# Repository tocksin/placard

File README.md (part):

# Placard
## PLA computer
This project is a computer designed using some Programmable Logic Arrays (PLA) 
or Programable Array Logic (PAL) or Programmable Array Devices (PLD) chips.  
This started as a pure 7400-series chip computer, but changed over to using 
some PLA/PLDs to increase the usability while not greatly increasing the chip 
count.  The first PLA was created in 1970 by Texas Instruments.  The PAL was 
created in 1978 by Monolithic Memories which is owned by Lattice Semi today. 
There are some differences between the three types of chips, but this project 
isn't going to distinguished between them.

The design documents are in [docs/](docs/README.md), grouped by subject.

## Project goals
The project has some hard-goals to maintain:
- Use only through-hole chips similar to the 7400-series DIP chips (or PLA of course)
- Use only active production chips.  No hunting sketchy websites for parts.
- Design true von Neumann CPU from scratch.  No Harvard.  Bare-metal programming on the computer is a must (native compiler).
- Have a video output.  The video standard is open, but probably a legacy output (VGA/Composite/etc).
- Make the instruction set "fun" to program.  This means no racing the beam to draw the screen.  Counting instructions is not fun.
- A PS/2 keyboard and mouse, read by the machine's own PLD receiver.  No USB.
- Native storage capabilities.  Need to be able to save/load programs as you create them on the computer.

## Block diagram
Each block shows how many chips it uses (33 and a 3.3 V regulator on the main board; the expansion and cartridge slots add none, the 32K ROM cartridge itself has 3).  See [docs/architecture/CHIPS.md](docs/architecture/CHIPS.md) for the parts.

The drawing is made by `src/scripts/gen_block_diagram.py` (CPU on the left, memory, I/O and audio in the middle, video on the right); rerun it when the design changes.

The I/O circuitry (SNES pads, SD card, PS/2 keyboard and mouse) is drawn as a schematic in
[docs/architecture/IO.md](docs/architecture/IO.md#schematic) (`schematics/placard_io_schematic.png`).
The audio circuitry (sample read, DAC register, R-2R ladder, audio line out jack) is drawn in
[docs/sound/SOUND.md](docs/sound/SOUND.md#schematic) (`schematics/placard_video_audio_schematic.png`).

The real schematic and PCB layout are a KiCad project in [kicad/](kicad/).

To build a board one chip at a time, testing each with a multimeter as it goes in, follow [docs/hardware/BRINGUP.md](docs/hardware/BRINGUP.md); it has a bring-up test ROM that checks the CPU and memory and shows the I/O on the screen.

## Memory Map
The Placard has 64kB of memory arranged in a 16-bit address bus and 8-bit databus.  The video RAM starts at x6020 and ends at xFFFF, and each row's mode byte (color mode and line repeat) is at x5A20 + row.  There is a 64kB RAM and a 64kB ROM behind the same addresses.  The address space is divided into eight 8kB sections, and a write-only map register at x5000 picks whether each section reads from the RAM or the ROM.

- **Writes always go to the RAM**, even in a section mapped to ROM.  The write strobe (/WE) is not decoded by address, so a write in the I/O window x5000-x53FF also lands in the RAM underneath it.
- **The map register** is a CD74ACT273E clocked by /MAP_WR from the I/O decode PLD; it latches the source bus at the end of the write.  Bit n = 1 makes section n read from RAM, 0 from ROM.  Bit 2 maps x4000-x4FFF and x5400-x5FFF, because x5000-x53FF is the I/O window.  It is write only, so software keeps a copy of the last value it wrote.
- **At power-up every section reads as ROM.**  RUN from the ROM cartridge holds the register's /MR low while the cartridge loads its SRAM and the CPU is held, so the CPU boots from ROM ([docs/architecture/ROM.md](docs/architecture/ROM.md#loading-the-cartridge)).
- **x5000-x53FF is the I/O window.**  The memory control PLD keeps both the RAM and the ROM off the bus there, so I/O always has priority.
- **Only `[Y,X]` reaches the I/O window**; `[0,D]` and `[0,X]` only address the zero page.
- **Video reads always read the RAM** (memory control PLD); only CPU reads follow the map.  The CPU can run code from the ROM under the video area while the screen shows the RAM, and a program that wants to read the video RAM maps that section to RAM.
- **The ROM is grouped by 8 KB section.**  The machine's 32K ROM (x8000-xFFFF, read at x0000-x7FFF too) holds the boot loader, the library, BASIC and a loader that runs the DOS and programs from the SD card, and each map section holds one kind of thing: section 7 what almost every program uses (jump table, core routines, PS/2 keyboard, pads, mouse, line input), section 6 the files (SD card driver, FAT reader and writer), section 5 BASIC, section 4 the loader, sound driver and font.  A program that maps a section to RAM gives up just that; the font is read through a zero page pointer (`FONT_PG`), so a program can put its own font anywhere.  The library runs in place.  The boot loader copies the library's RAM code to x1F00, gives each expansion card a chance to run its own boot code (like the Apple II), then maps sections 0 and 2 to RAM (map = 05) and starts the loader.  A development ROM (64K cartridge) adds one program in the first 32K, run in place at x6000-x7FFF and x2000-x3FFF, or copied to RAM x0000 for the older demos.  See [docs/architecture/ROM.md](docs/architecture/ROM.md) and [docs/software/DOS.md](docs/software/DOS.md).
- **After a map write**, the next instruction must not be fetched from a section whose map bit that write changed, unless the ROM and RAM hold the same byte there (the new map arrives 2.6 ns too late for that fetch).  Copying the ROM into the RAM underneath and then switching the section is safe.  See [docs/timing/TIMING.md](docs/timing/TIMING.md#video-and-the-rest).

The memory control PLD (`ATF22V10_MEM_CTRL.pld`) makes /ROM_OE and /RAM_OE from the address, the map, RW and PIXEL_ENABLE, using only the low half of each clock.  The RAM's /WE comes from the Sync PLD, off an early tap of the clock ([docs/timing/WE_TIMING.md](docs/timing/WE_TIMING.md)).  The I/O decode PLD (`ATF22V10_IO_DECODE.pld`) makes the upper RAM/ROM chip select (/CE_HI) and the I/O strobes.

The RAM is two AS7C256C-15PCN (32K × 8, 15 ns) chips.  The ROM is one more AS7C256C-15PCN on the 32K ROM cartridge, loaded at power-up from one AT28C256 EEPROM by the cartridge while it stalls the CPU ([docs/architecture/ROM.md](docs/architecture/ROM.md#loading-the-cartridge)).  See [docs/architecture/CPU.md](docs/architecture/CPU.md#memory-parts) and [docs/timing/TIMING.md](docs/timing/TIMING.md).

| Address | Map bit | Function  |
|---------|---------|------|
| x0000-x1FFF | 0 | RAM/ROM (zero page, program variables, library RAM code at x1F00; ROM: reset jump) |
| x2000-x3FFF | 1 | RAM/ROM (development ROM: program) |
| x4000-x4FFF | 2 | RAM/ROM (program data; FAT variables and buffer at x4D00-x4FFF) |
| x5000-x53FF | none | I/O window (see below) |
| x5400-x5FFF | 2 | RAM/ROM (mode bytes at x5A20-x5BFF, audio buffer at x5DF3-x5FFF) |
| x6000-x7FFF | 3 | RAM/ROM (Video Memory from x6020; development ROM: program from x6000) |
| x8000-x9FFF | 4 | RAM/ROM (Video Memory; ROM: vectors x8000, loader and the end of BASIC x8100, sound driver x9200, font x9700, LIB_RAM copy x9F00) |
| xA000-xBFFF | 5 | RAM/ROM (Video Memory; ROM: BASIC) |
| xC000-xDFFF | 6 | RAM/ROM (Video Memory; ROM: files: SD card driver xC000, FAT reader xC800, FAT writer xD600) |
| xE000-xFFFF | 7 | RAM/ROM (Video Memory; ROM: PS/2 keyboard, pads, mouse, line input, menu hook, slot helpers, core routines xF400, jump table xFB00, boot loader xFD00) |

The drawing is made by `src/scripts/gen_memory_map.py`; rerun it when the map changes.

### I/O window
Each I/O page has its own select from the I/O decode PLD (revision 07), made straight from the address and valid about 13 ns into the clock.  A write is the select with /WE: devices latch the source bus on the rising edge at the end of /WE.  A read is the select with Q0 low (the LOAD_MEM clock, when the CPU latches the bus into D), and nothing waits for STALL.  The shared port is described in [docs/architecture/IO.md](docs/architecture/IO.md) and the expansion slots in [docs/architecture/EXPANSION.md](docs/architecture/EXPANSION.md).

| Address | Select | R/W | Function |
|---------|--------|-----|----------|
| x5000-x50FF | /P0 (write: /MAP_WR from the Sync PLD) | W | ROM/RAM map register (built) |
| x5000-x50FF | /P0 and Q0 | R | Video line counter, V9:V2 (built) |
| x5100-x517F | /EXP1 | R/W | Expansion slot 1 |
| x5180-x51FF | /EXP3 | R/W | Expansion slot 3 |
| x5200-x52FF | /PORT and /WE | W | Shared port latch (port PLD registers): SD card SCK, MOSI and /CS, SNES pad clock and latch, PS/2 lines; a write to x5202/x5203 also re-arms the PS/2 receiver |
| x5200-x52FF | /PORT and Q0 | R | Shared port: SD MISO and the free PS/2 clock (x5200), SNES pad data (x5201), PS/2 receiver byte (x5202) and ready flag (x5203) |
| x5300-x537F | /EXP2 | R/W | Expansion slot 2 |
| x5380-x53FF | /EXP4 | R/W | Expansion slot 4 |

### Sound
The video circuit reads one 8-bit sample per scan line from x5DF3-x5FFF (525 bytes, one frame) and plays it through a 74HCT574 and a resistor ladder DAC, at the line rate of 31.47 kHz.  80h is silence.  The library's sound driver (`snd_update` once a frame, with `snd_tone`, `snd_beep`, `snd_note`, `snd_noise` and `snd_play`) refills the buffer behind the line being played.  See [docs/sound/SOUND.md](docs/sound/SOUND.md).

### Video line read
A read anywhere in x5000-x50FF returns the upper 8 bits of the video line counter, V9:V2.  The V counter in the V Counter PLD counts 499 to 1023, and one 74F541 enabled by /P0 and Q0 puts V9:V2 on the data bus.  The ROM/RAM map register shares the page but is write only, so there is no conflict.  Read it with `ld 0x50, y` then `ld [y,x], ac`.

- **It is a single byte**, so it can't tear between reads.
- **Resolution is 4 lines** (128 us).  Visible rows start at V = 544, so `row / 4 = value - 136`.  A value below 136 means vertical blanking.
- **There is no frame counter.**  Software keeps time by polling: each time the value goes down (from 255 back to 124), a frame has passed.  At the FPGA's 25.000 MHz clock a frame is 525 lines, about 16.8 ms (59.5 Hz).
- **Software must poll at least once per frame**, or it misses a wrap.  Elapsed time is then frames x 16.8 ms plus the line position for finer detail.

## Video
The video is designed to be 640x480 VGA 60Hz standard.  This means a 25.175 MHz clock.  This requires two counters: a horizontal and vertical.  They count 800 and 600 pixels.  This needs a 10-bit counter for each.  The counters form the RAM address space to read the pixel values.  The video memory is organized in a non-traditional way with H,V instead of V,H.

### Line repeat
Bits 3:2 of a row's mode byte make each byte of video memory show on 1, 2 or 4 lines (640 × 480, 240 or 120).  A full 2x screen leaves 20 KB of the video area free (the even pages x60, x62 ... xFE) and a full 4x screen 30 KB.  The audio slot PLD remaps four row address bits, so no chips were added.  See [docs/video/VIDEO.md](docs/video/VIDEO.md#line-repeat).

### Text demo
`src/scripts/text_demo.asm` draws a demo screen with the CPU and keeps a test running on it: 80 column text (2 colors, 1x, under row tints: blocks of the 7 tints roll down over the text, with a second of rest between), a 16 color band (4 bpp, 4x), 40 column text (2 bpp, 2x) and a 256 color band (8 bpp, 4x) with "256" in shades of red, blue and green and a turning rainbow ring.  Each frame it tests one page of RAM (85 pages: x0100-x1EFF, x2000-x4FFF, x5400-x59FF and x5C00-x5CFF, 14 patterns each, with a progress bar, pass and error counts) and updates a frame counter, an uptime clock, a spinner, a turning color wheel, the ring and a message that scrolls a pixel a frame.  H shows the same picture on the 160-read rows of a rev B board (80 column text in 4 colors, 16 colors at 320 across, 256 colors at 160 across: smoothed letters and digits, round wheel dots, a rounder ring; [docs/video/HIRES.md](docs/video/HIRES.md)) and back.  It runs from the SD card (`TEXT.PLC`, `gen_text_demo_sd.py`, in the demo menu), and `src/scripts/text_demo_sim.py` runs and checks it in the simulator (`--gif` makes an animation).  `gen_text_demo_sd.py` makes the SD card version (`TEXT.PLC`, in the demo menu), whose RAM test covers only the RAM the program leaves free ([docs/software/MENU.md](docs/software/MENU.md#the-text-demo-on-the-card)).

### DOS, BASIC and demo menu
The machine ships the 32K ROM image (`src/scripts/rom32.masm`, `build\rom32.bat`): the boot loader, the library, PLACARD BASIC (a 16-bit integer BASIC with strings, graphics, sound and SAVE/LOAD on the card, [docs/software/BASIC.md](docs/software/BASIC.md)) and a loader that runs `.PLC` programs from the SD card.  The DOS is one of those programs (`DOS.PLC`, `src/scripts/dos.masm`).  At power-up the loader runs the program named in `BOOT.CFG`, or the DOS's file browser (hold Esc) that runs, deletes and picks the boot program, with a command line for `LOAD` and `SAVE` of memory as files.  With no card, or no `DOS.PLC` on it, BASIC starts.  Ctrl+B in the browser starts BASIC.  The demo menu is one of those programs (`MENU.PLC`, `src/scripts/menu.masm`): the CPU test, pi, Mandelbrot, the Game of Life, the Boing ball, the 3D ships, the ray caster, the side scroller, the textured ray caster and the text demo run in turn, each until it is done or for 2 minutes (Mandelbrot 3); Esc in any program shows the menu (Up / Down and Enter, or 1-9 and 0), a program picked there runs until Esc, and after 2 minutes with no key the menu goes back to running them in turn.  The `sdcard/` folder holds the files for the card; `src/scripts/test_dos.py`, `test_menu.py` and `test_basic.py` check them in the simulator; the `.BAS` files on the card are BASIC examples.  See [docs/software/DOS.md](docs/software/DOS.md), [docs/software/MENU.md](docs/software/MENU.md) and [docs/architecture/ROM.md](docs/architecture/ROM.md#the-32k-image).

### Pinboard
`sdcard/PINBOARD.PLC` (`src/scripts/pinboard.masm`, `pinboard.vm`, `gen_pinboard.py`) is a windowed desktop: cards pinned on a board, moved, stacked and taken down with the PS/2 mouse or the keys.  The Files card browses the SD card, runs its programs, shows its pictures in the photo viewer and plays its sound files in the sound player, and Pinboard comes back when one ends; the Clock card keeps the time you set, the Calc card is a whole-number calculator, and the Editor card edits a text file from the card and saves it.  The Display card switches the screen between 640 x 480 in 2 colors and, on a rev B board, 640 x 240 in 4 colors or 320 x 240 in 16.  It is written in the language of BASIC's interpreter, with machine code for the characters and the pointer.  `src/scripts/test_pinboard.py` checks it in the emulator's core ([docs/software/PINBOARD.md](docs/software/PINBOARD.md)).

### Game demos
Four demos show what the CPU can do with no sprite or collision hardware.  The first three are written by a Python generator (the tables, the unrolled drawing code and a bit-exact model of the picture), and each has a simulator test that checks every frame against the model.

`sdcard/RAYCAST.PLC` (`gen_raycast.py`, which writes `src/scripts/raycast_sd.asm`) is a ray caster: an 80 × 112 view at 8 bpp (4x line repeat) of a maze with shaded, two-tone walls and a dithered floor and ceiling, walked by a demo script until a key or pad button takes over (arrow keys or SNES pad 1: Up / Down walk, Left / Right turn).  A view takes 143k-170k clocks (a column about 2,000), so it runs at the full 60 views a second using under 40 % of each frame.  It is in the demo menu and `src/scripts/test_raycast_sim.py` checks it.

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
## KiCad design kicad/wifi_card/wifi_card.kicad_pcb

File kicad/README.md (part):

# KiCad project

Date: 2026-11-21

The Placard schematic and PCB layout, one KiCad project for the main board
and one for each cartridge.  The files are saved by KiCad 9, so open them
with KiCad 9 or newer.  Board revisions are in
[docs/hardware/RELEASES.md](../docs/hardware/RELEASES.md): rev A is the
board as ordered (git tag `rev-A`), and the files here are the working
rev B.

| File | What it is |
|------|------------|
| `placard.kicad_pro` | the project; open this in KiCad |
| `placard.kicad_sch` | the schematic's root sheet (A3): one box per sheet, laid out like the block diagram |
| `power.kicad_sch` ... `expansion.kicad_sch` | the ten sheets (power and clock, control, PC and address mux, ALU and registers, data bus, memory and I/O decode, video timing, video and audio out, shared port, expansion slots), docs/hardware/SCHEMATIC_PLAN.md |
| `cartridge_64k/` | the 64K ROM cartridge (5 chips), its own project (`cartridge_64k.kicad_pro`, one sheet and a routed 4-layer board), using the same `lib/` |
| `cartridge_32k/` | the 32K ROM cartridge (3 chips), its own project (`cartridge_32k.kicad_pro`, one sheet and a routed 4-layer board), using the same `lib/`; mounting hole H1 at the same place as on the 64K board |
| `memory_card/` | the 512K memory expansion card (3 chips, docs/architecture/MEMCARD.md), its own project (`memory_card.kicad_pro`, one sheet and a routed board), using the same `lib/`.  The sheet is written by `gen_kicad_schematic.py --memcard`, which leaves the other sheets alone, and the board by `gen_kicad_memcard_pcb.py` (KiCad 9), which keeps an existing board unless run with `--force` |
| `wifi_card/` | the WiFi expansion card (one PLD and an ESP32-C3-DevKitM-1 board, docs/architecture/WIFICARD.md), its own project (`wifi_card.kicad_pro`, one sheet and a board with the parts placed, not routed), using the same `lib/`.  The sheet is written by `gen_kicad_schematic.py --wificard` and the board by `gen_kicad_wificard_pcb.py` (KiCad 9), which keeps an existing board unless run with `--force` |
| `placard.kicad_pcb` | the main board, routed: 4 layers (F.Cu, In1.Cu = GND, In2.Cu = VCC, B.Cu) |
| `lib/placard.kicad_sym` | PLD symbols: `ATF22V10C` (generic) and one `ATF22V10C_<name>` per `.pld` file, with its pin names |
| `lib/placard_parts.kicad_sym` | other project symbols: `AS7C256C` SRAM, `Expansion_Slot`, `Cartridge_Slot`, `SNES_Pad_Socket`, `PS2_Dual_Stacked`, `USB_C_Power` |
| `lib/placard_std.kicad_sym` | copies of the stock KiCad symbols the sheets use (74xx, R, C, D, connectors, regulator, the cartridge EEPROM `28C256`, and the power symbols `+5V`, `GND`, `+3V3`, `GNDA`, `PWR_FLAG`) with larger pin text, written by `src/scripts/gen_kicad_std.py` |
| `lib/placard.pretty/` | project footprints: the main board's connectors and switches (written by `src/scripts/gen_kicad_connectors.py`), and kit versions of KiCad's DIP socket footprints (`DIP-nn_..._Socket_Puller`: chip-puller room on User.Eco1, part number in silkscreen) and of the axial resistor (`..._Value`: value in silkscreen), written by `src/scripts/gen_kicad_kit_footprints.py`, and copies of the KiCad 9.0.6 footprints the boards use (capacitors, diodes, LED, pin header, oscillator, TO-92, SIP resistor array, mounting holes, net tie; KiCad 9 format), written by `src/scripts/gen_kicad_stock_footprints.py` |
| `lib/placard.3dshapes/` | 3D models (STEP) for the connectors, switches and polyfuse, named after their footprints and referenced as `${KIPRJMOD}/lib/placard.3dshapes/...`, so they show in any KiCad version without a 3D library path; written by `src/scripts/gen_kicad_3d_models.py` (CadQuery), which also copies in KiCad's own models for SW2, J7 and J13, and KiCad's models for the stock, socket and resistor footprints, copied by `src/scripts/gen_kicad_stock_footprints.py` |
| `sym-lib-table`, `fp-lib-table` | point KiCad at the project libraries |
| `fab/` | the rev A Gerber and drill files as ordered ([fab/README.md](fab/README.md)) |

The main board is 290 x 215 mm (290 wide, the keyboard's width; 215 deep, so
kit builders have room), 4 layers, placed and routed.

The back edge carries USB-C power, audio line out, VGA and the stacked PS/2;
the left side the power switch, reset button and SD card; the front edge the
two SNES ports.  The cartridge and the four expansion cards stand up
through the case top.  Every DIP sits in a socket footprint with 2.5 mm of
chip-puller room clear past each socket end, and Cn sits beside Un.
`src/scripts/gen_board_pictures.py` draws the two pictures (and the
cartridge pictures in [EXPANSION.md](../docs/architecture/EXPANSION.md))
from the board files without changing them; rerun it after a layout change.

The board file is edited in KiCad and by the autorouter, so it is the
source.  `src/scripts/gen_kicad_pcb.py` made the first outline and placement
and `src/scripts/gen_kicad_cart_pcb.py` the cartridges' placement; do not
run either on the boards now (the cartridge script leaves an existing board
alone unless given `--force`).  The first placement drawings are in
[docs/archive/](../docs/archive/README.md).

The footprints KiCad has no part for (cartridge slot, expansion slots,
PS/2, SNES, the power switch, the relay) are written by
`src/scripts/gen_kicad_connectors.py`.  The SNES sockets were measured from
the part; the others are drawn from typical dimensions for the part family,
so check them against the parts when the rev A boards arrive.
Their 3D models (`src/scripts/gen_kicad_3d_models.py`) are drawn at typical
dimensions too, with the leads put on the footprint pads.  J4 (SD), J7 (VGA),
F1 and SW2 use project copies of KiCad's footprints (`placard:` library) only so
they can point at the project's models; the pads are KiCad's.
The schematic rules (which chips go on which sheet, numbering, and how
the sheets are drawn) are in [docs/hardware/SCHEMATIC_PLAN.md](../docs/hardware/SCHEMATIC_PLAN.md).  Parts and U-numbers come from
[docs/architecture/CHIPS.md](../docs/architecture/CHIPS.md); the PLD pinouts come from the `.pld` files
in `src/`.

Every part carries Manufacturer and MPN fields (empty where no part number
is chosen yet), set from the `MPN` table in `src/scripts/gen_kicad_schematic.py`,
so KiCad's BOM export lists them.  `src/scripts/gen_bom.py` writes one grouped
bill of materials per assembly (main board, 64K and 32K cartridges, case),
indexed in [docs/bom/BOM.md](../docs/bom/BOM.md), each as .md and .csv, including the
bare PCBs, sockets, shells and screws that are not on the schematic.

Backups, autosaves, lock files, `*.kicad_prl` (per-user view settings) and
`fp-info-cache` are git-ignored.

## PLD symbols

`src/scripts/gen_kicad_symbols.py` writes `lib/placard.kicad_sym` from the
`PIN` statements in `src/pld/*.pld`; rerun it after changing a PLD's pins
(it overwrites the whole library).  The pins are placed for the schematic,
not in pin-number order: the script's `LAYOUT` table puts inputs on the
left and outputs on the right, buses together in bit order, and each
function's pins in their own group.  Where one PLD does two unrelated jobs
(the audio PLD's /AC_SEL, the port PLD's pad read, the memory control's
RUN input) a dashed line across the box separates them.  Active-low pins are
`/NAME`, VCC (24) is on top and GND (12) underneath, unused pins are `nc`
(no-connect type), and the `.pld` file name is under the part number.  The
script stops if a `.pld`'s pins and its `LAYOUT` entry no longer match.
Each symbol has the footprint `Package_DIP:DIP-24_W7.62mm` and the
ATF22V10C datasheet link.

## Other symbols

`src/scripts/gen_kicad_parts.py` writes `lib/placard_parts.kicad_sym`, in
the same style, for the parts KiCad's libraries do not have: the AS7C256C
SRAM, the expansion slot (Molex 87715-9106 as the cartridge slot, contacts A1-A32 and B1-B32)
and the cartridge slot (Molex 87715-9106, 2 x 32 keyed, contacts A1-A32
and B1-B32), as in EXPANSION.md, with the +5 V and GND contacts stacked on
one pin each, the SNES pad socket (IO.md) and
`USB_C_Power`, the 5 V input: a power-only 6-contact USB-C receptacle
(GCT USB4125, footprint `placard:USB_C_Receptacle_GCT_USB4125_6P_HandSolder`:
KiCad's USB4125 footprint with the SMD pads 1.5 mm longer for the iron, made by gen_kicad_connectors.py)
with a 5.1k resistor from CC1 and from CC2 to GND so a charger gives 5 V.  Make
changes in the script, since rerunning it overwrites the library.

Every symbol, footprint and 3D model the sheets and boards use is in `lib/`
(since 2026-10-26): the projects' library tables list only the placard
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
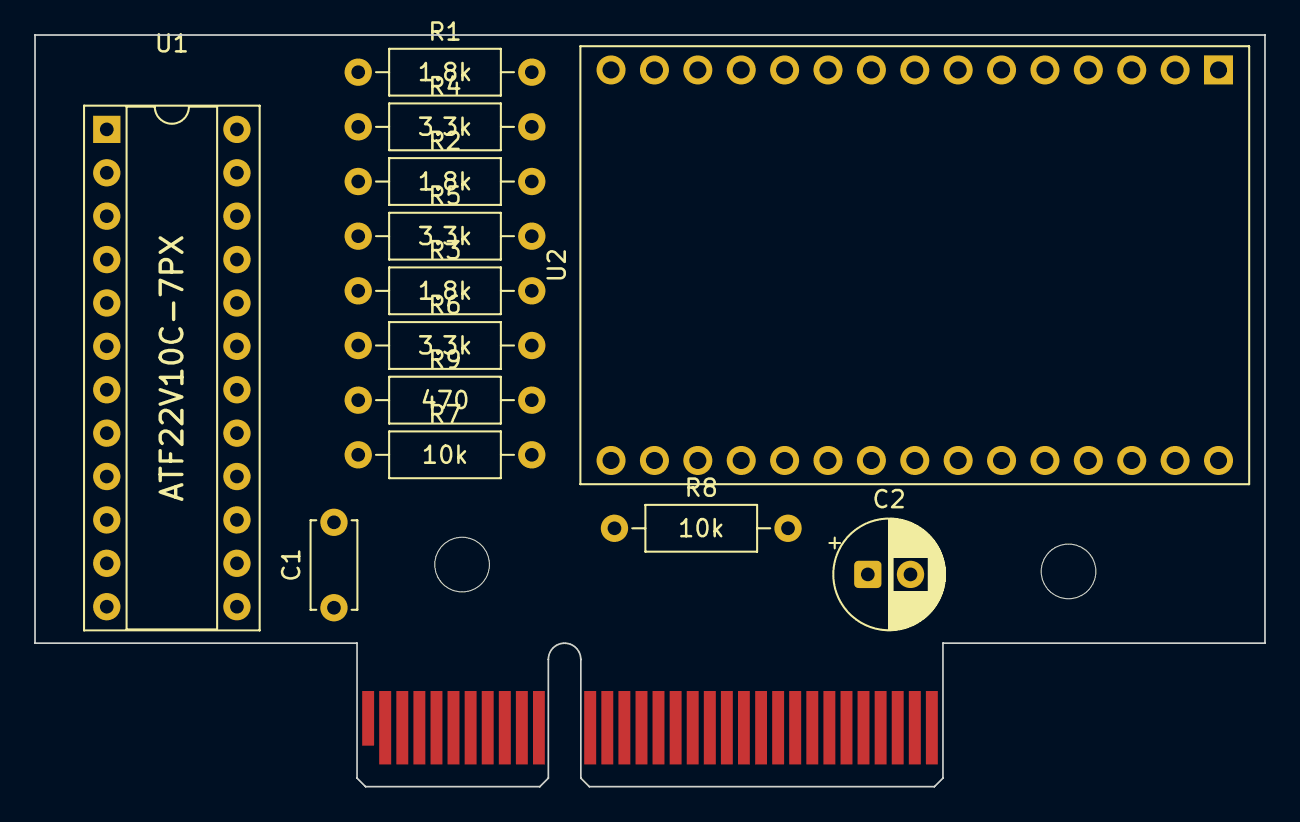
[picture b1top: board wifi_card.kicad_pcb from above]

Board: 4 copper layers, 72.0 x 44.0 mm, 16 parts (0 on the bottom side), 26 nets, no tracks yet.

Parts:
C1: 100n; C_Disc_D5.0mm_W2.5mm_P5.00mm
C2: 220u; CP_Radial_D6.3mm_P2.50mm
H1, H2: M3; MountingHole_3.2mm_M3
J1: Card edge (87715-9106 mate); Card_Edge_87715-9106
R1, R2, R3: 1.8k; R_Axial_DIN0207_L6.3mm_D2.5mm_P10.16mm_Horizontal_Value
R4, R5, R6: 3.3k; R_Axial_DIN0207_L6.3mm_D2.5mm_P10.16mm_Horizontal_Value
R7, R8: 10k; R_Axial_DIN0207_L6.3mm_D2.5mm_P10.16mm_Horizontal_Value
R9: 470; R_Axial_DIN0207_L6.3mm_D2.5mm_P10.16mm_Horizontal_Value
U1: ATF22V10C-7PX; DIP-24_W7.62mm_Socket_Puller
U2: ESP32-C3-DevKitM-1-N4X; ESP32-C3-DevKitM-1

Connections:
+5V: C1.1, C2.1, J1.A2, J1.B2, U1.24, U2.13, U2.14
/DATABUS0: J1.A23, U1.7
/DATABUS1: J1.B13, U1.8
/DATABUS2: J1.B15, U1.18
/DATABUS3: J1.B17, U1.19
/DATABUS4: J1.B19, U1.20
/DATABUS5: J1.B23, U1.21
/DATABUS6: J1.B25, U1.22
/DATABUS7: J1.B29, U1.23
GND: C1.2, C2.2, J1.A1, J1.A11, J1.A12, J1.A21, J1.A31, J1.B1, J1.B11, J1.B18, J1.B21, J1.B26, J1.B30, J1.B31, J1.B32, R4.2, R5.2, R6.2, R7.2, R8.2, U1.12, U2.6, U2.8, U2.12, U2.15, U2.19, U2.22, U2.27, U2.30
unnamed: J1.A22, U1.4
unnamed: J1.B9, U1.5
unnamed: J1.B7, U1.6
unnamed: J1.A10, U1.3
unnamed: J1.A16, U1.2
unnamed: J1.B24, U1.1
unnamed: R7.1, U1.9, U2.25
unnamed: R8.1, U1.10, U2.26
unnamed: R3.1, U1.16
unnamed: R2.1, U1.15
unnamed: R9.1, U1.17
unnamed: R1.1, U1.14
unnamed: R1.2, R4.1, U2.24
unnamed: R2.2, R5.1, U2.23
unnamed: R3.2, R6.1, U2.11
unnamed: R9.2, U2.7

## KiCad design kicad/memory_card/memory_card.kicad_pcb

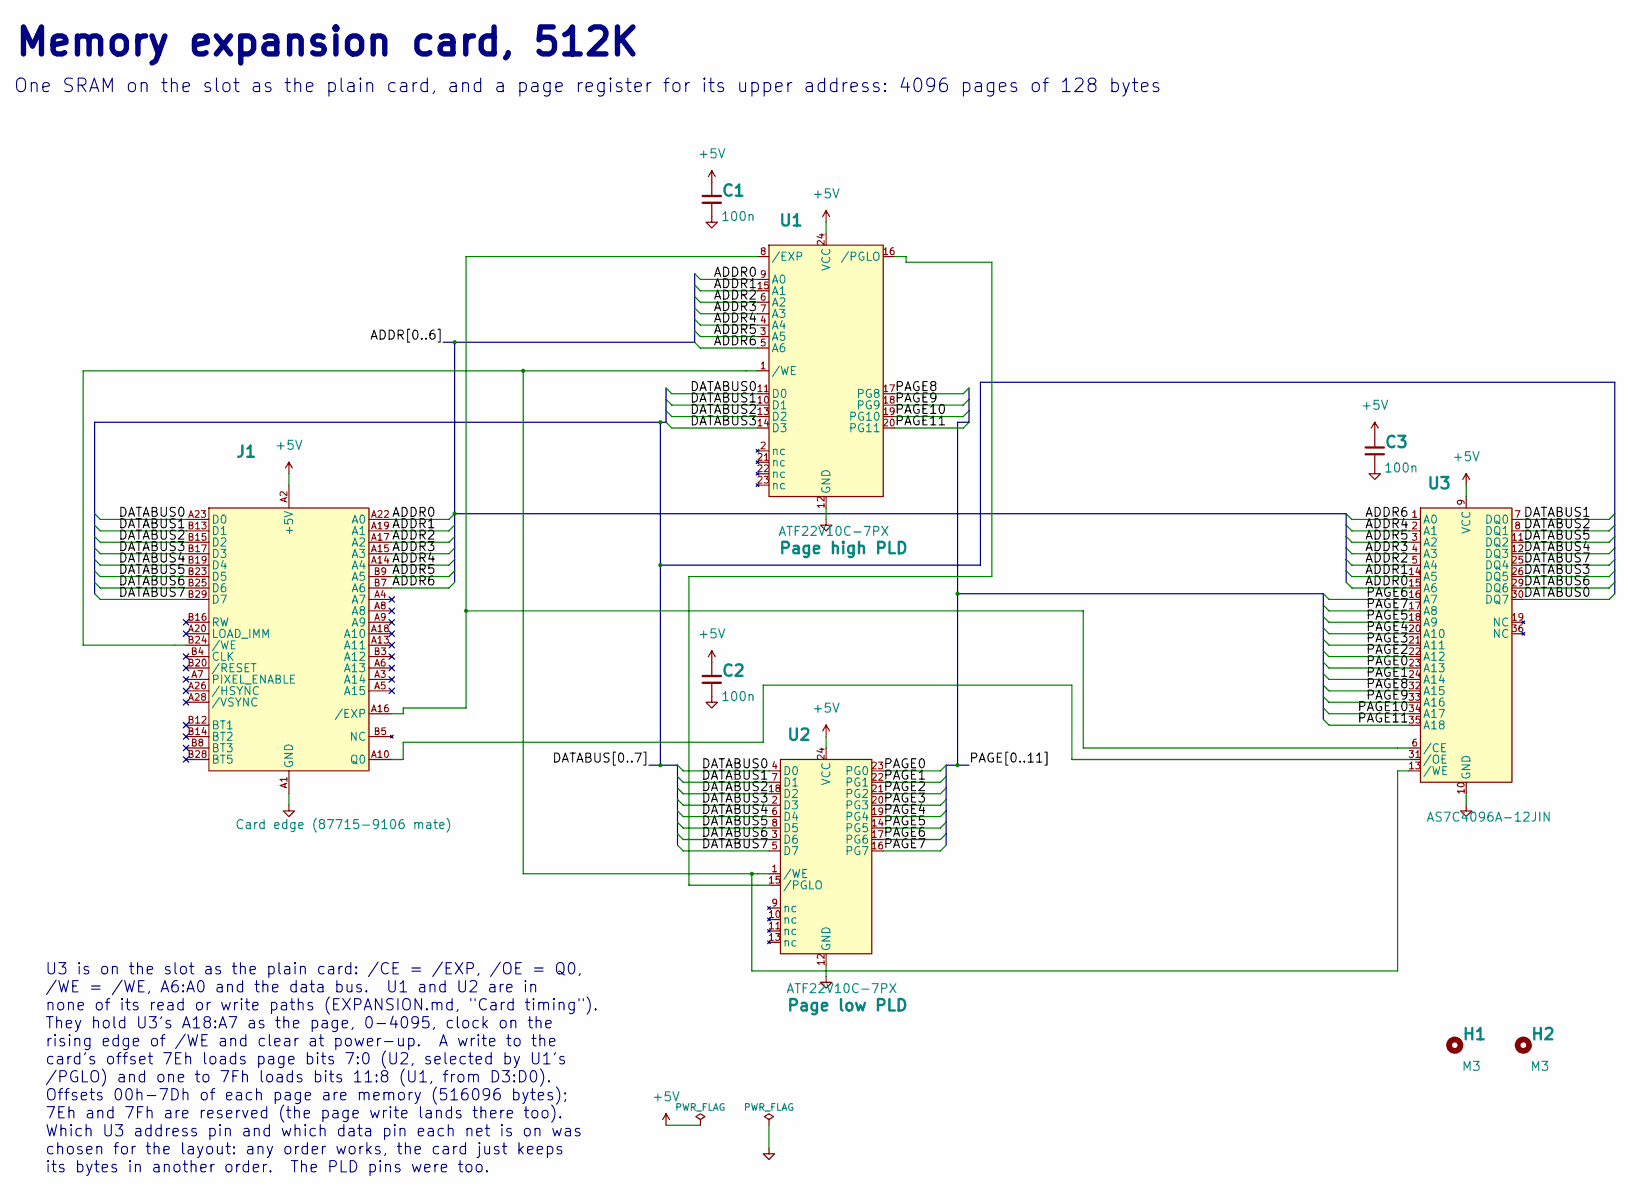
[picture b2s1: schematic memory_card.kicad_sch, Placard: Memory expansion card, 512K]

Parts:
C1, C2, C3: 100n; C_Disc_D5.0mm_W2.5mm_P5.00mm; MPN FG28X7R1H104KNT00
H1, H2: M3; MountingHole_3.2mm_M3
J1: Card edge (87715-9106 mate); Card_Edge_87715-9106
U1, U2: ATF22V10C-7PX; DIP-24_W7.62mm_Socket_Puller; MPN ATF22V10C-7PX
U3: AS7C4096A-12JIN; SOJ-36_10.16x23.495mm_P1.27mm; MPN AS7C4096A-12JIN

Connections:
+5V: C1.1, C2.1, C3.1, J1.A2 (+5V), J1.B2 (+5V), U1.24 (VCC), U2.24 (VCC), U3.9 (VCC), U3.27 (VCC)
/ADDR0: J1.A22 (A0), U1.9 (A0), U3.15 (A6)
/ADDR1: J1.A19 (A1), U1.15 (A1), U3.14 (A5)
/ADDR2: J1.A17 (A2), U1.6 (A2), U3.5 (A4)
/ADDR3: J1.A15 (A3), U1.7 (A3), U3.4 (A3)
/ADDR4: J1.A14 (A4), U1.4 (A4), U3.2 (A1)
/ADDR5: J1.B9 (A5), U1.3 (A5), U3.3 (A2)
/ADDR6: J1.B7 (A6), U1.5 (A6), U3.1 (A0)
/DATABUS0: J1.A23 (D0), U1.11 (D0), U2.4 (D0), U3.30 (DQ7)
/DATABUS1: J1.B13 (D1), U1.10 (D1), U2.7 (D1), U3.7 (DQ0)
/DATABUS2: J1.B15 (D2), U1.13 (D2), U2.18 (D2), U3.8 (DQ1)
/DATABUS3: J1.B17 (D3), U1.14 (D3), U2.2 (D3), U3.26 (DQ5)
/DATABUS4: J1.B19 (D4), U2.6 (D4), U3.12 (DQ3)
/DATABUS5: J1.B23 (D5), U2.8 (D5), U3.11 (DQ2)
/DATABUS6: J1.B25 (D6), U2.3 (D6), U3.29 (DQ6)
/DATABUS7: J1.B29 (D7), U2.5 (D7), U3.25 (DQ4)
/PAGE0: U2.23 (PG0), U3.23 (A13)
/PAGE1: U2.22 (PG1), U3.24 (A14)
/PAGE2: U2.21 (PG2), U3.22 (A12)
/PAGE3: U2.20 (PG3), U3.21 (A11)
/PAGE4: U2.19 (PG4), U3.20 (A10)
/PAGE5: U2.14 (PG5), U3.18 (A9)
/PAGE6: U2.17 (PG6), U3.16 (A7)
/PAGE7: U2.16 (PG7), U3.17 (A8)
/PAGE8: U1.17 (PG8), U3.32 (A15)
/PAGE9: U1.18 (PG9), U3.33 (A16)
/PAGE10: U1.19 (PG10), U3.34 (A17)
/PAGE11: U1.20 (PG11), U3.35 (A18)
GND: C1.2, C2.2, C3.2, J1.A1 (GND), J1.A11 (GND), J1.A12 (GND), J1.A21 (GND), J1.A31 (GND), J1.B1 (GND), J1.B11 (GND), J1.B18 (GND), J1.B21 (GND), J1.B26 (GND), J1.B30 (GND), J1.B31 (GND), J1.B32 (GND), U1.12 (GND), U2.12 (GND), U3.10 (GND), U3.28 (GND)
unnamed: J1.A10 (Q0), U3.31 (/OE)
unnamed: J1.A16 (/EXP), U1.8 (/EXP), U3.6 (/CE)
unnamed: J1.B24 (/WE), U1.1 (/WE), U2.1 (/WE), U3.13 (/WE)
unnamed: U1.16 (/PGLO), U2.15 (/PGLO)

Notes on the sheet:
Memory expansion card, 512K
One SRAM on the slot as the plain card, and a page register for its upper address: 4096 pages of 128 bytes
U3 is on the slot as the plain card: /CE = /EXP, /OE = Q0,
/WE = /WE, A6:A0 and the data bus. U1 and U2 are in
none of its read or write paths (EXPANSION.md, "Card timing").
They hold U3's A18:A7 as the page, 0-4095, clock on the
rising edge of /WE and clear at power-up. A write to the
card's offset 7Eh loads page bits 7:0 (U2, selected by U1's
/PGLO) and one to 7Fh loads bits 11:8 (U1, from D3:D0).
Offsets 00h-7Dh of each page are memory (516096 bytes);
7Eh and 7Fh are reserved (the page write lands there too).
Which U3 address pin and which data pin each net is on was
chosen for the layout: any order works, the card just keeps
its bytes in another order. The PLD pins were too.

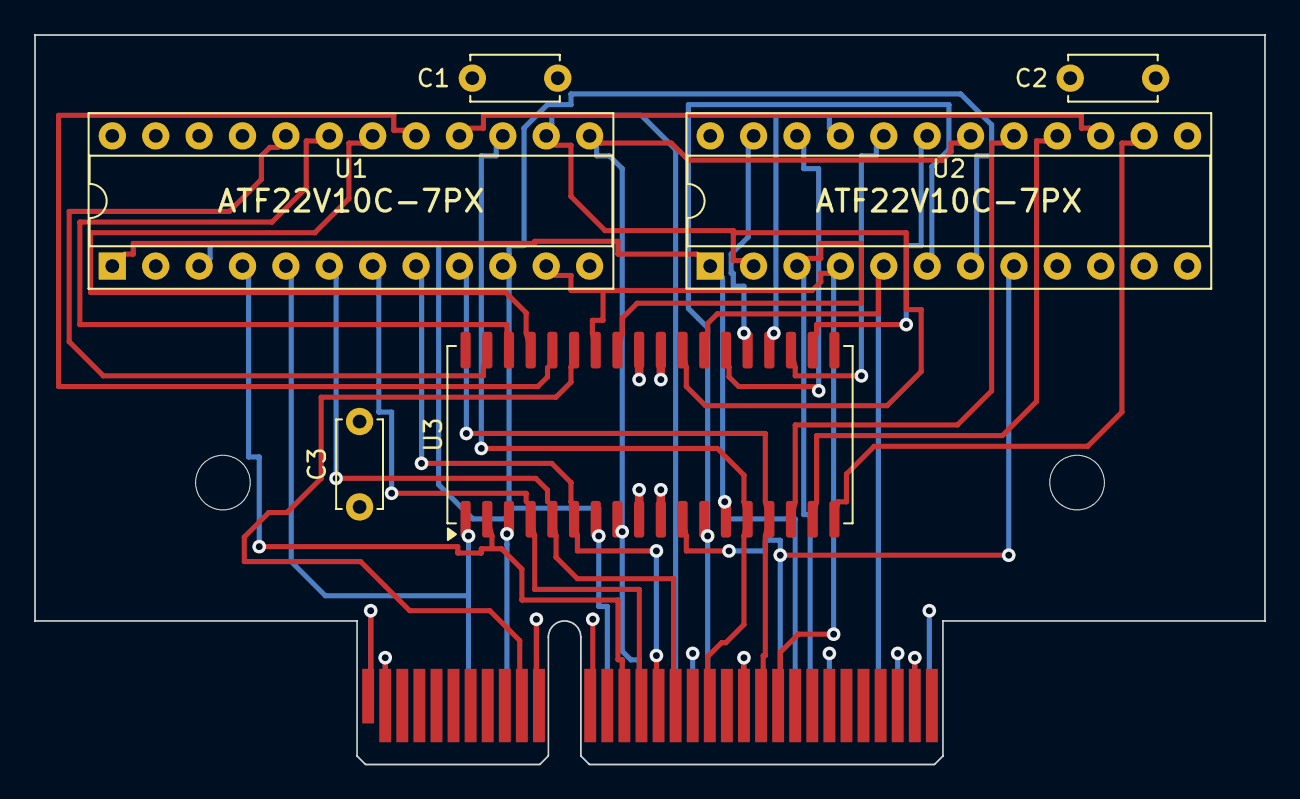
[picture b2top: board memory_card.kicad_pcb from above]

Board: 4 copper layers, 72.0 x 42.7 mm, 9 parts (0 on the bottom side), 33 nets.

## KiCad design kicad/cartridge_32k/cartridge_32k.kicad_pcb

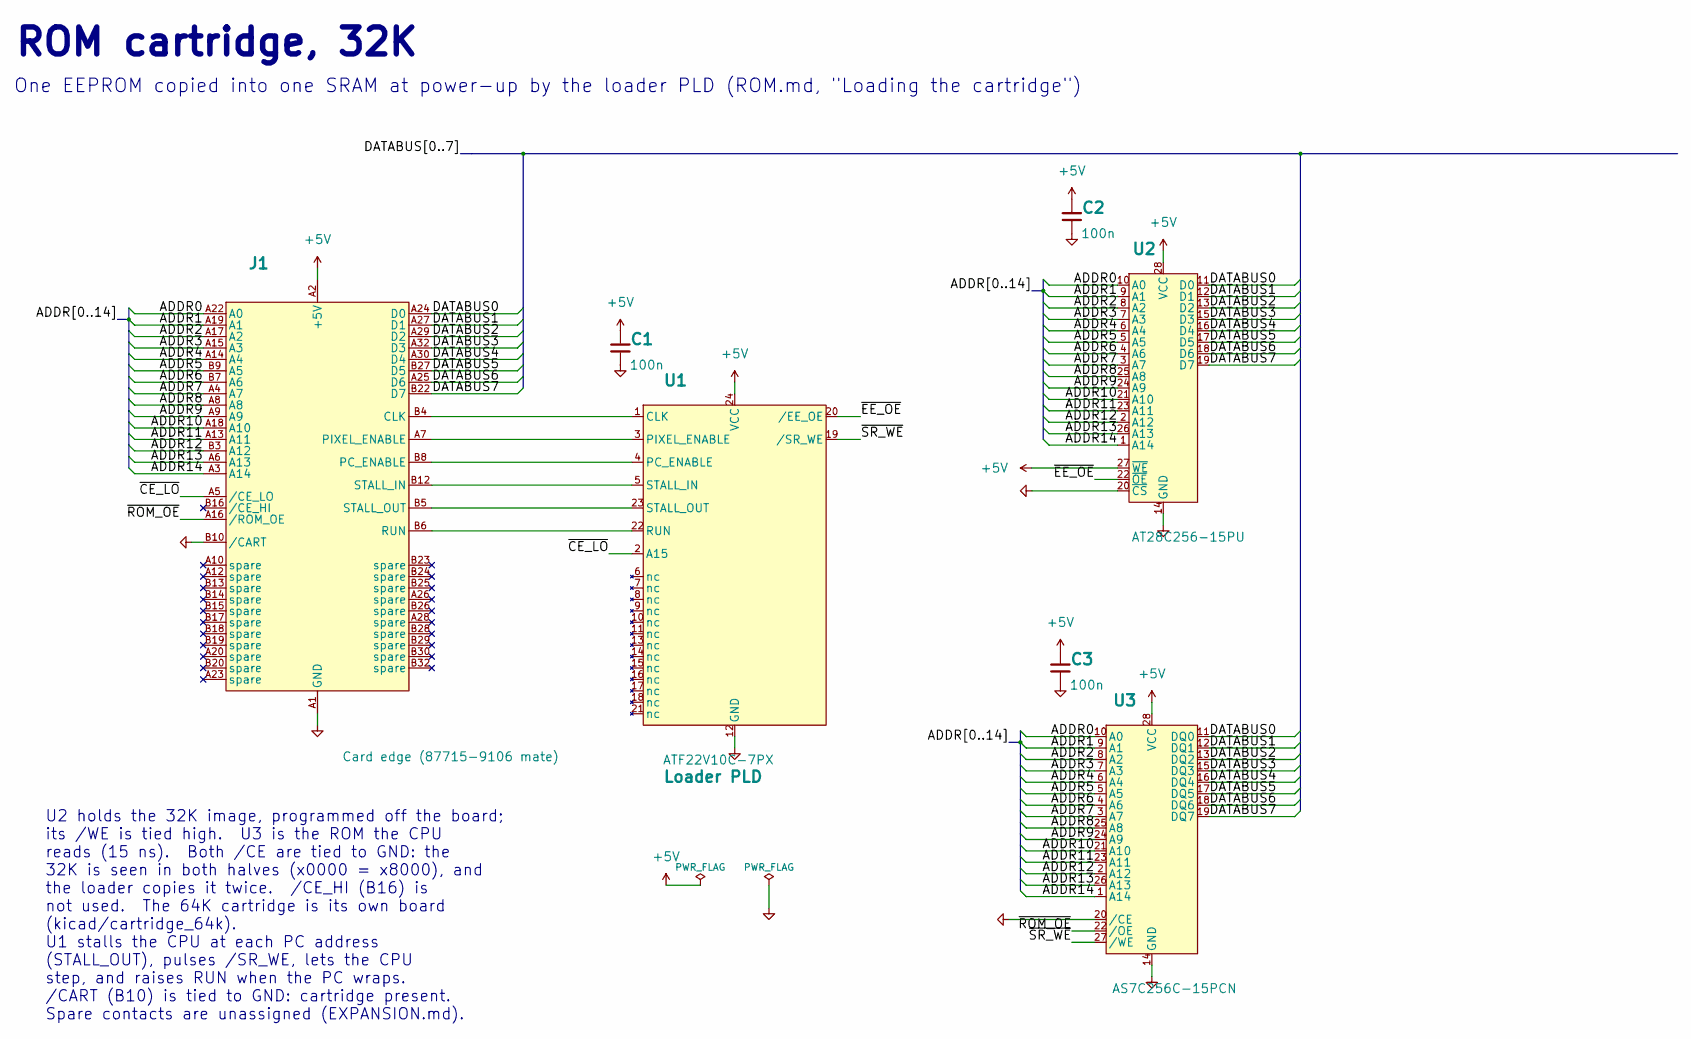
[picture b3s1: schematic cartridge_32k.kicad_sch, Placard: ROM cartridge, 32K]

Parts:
C1, C2, C3: 100n; C_Disc_D5.0mm_W2.5mm_P5.00mm; MPN FG28X7R1H104KNT00
J1: Card edge (87715-9106 mate); Card_Edge_87715-9106
U1: ATF22V10C-7PX; DIP-24_W7.62mm_Socket_Puller; MPN ATF22V10C-7PX
U2: AT28C256-15PU; DIP-28_W15.24mm_Socket_Puller; MPN AT28C256-15PU
U3: AS7C256C-15PCN; DIP-28_W7.62mm_Socket_Puller; MPN AS7C256C-15PCN

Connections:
+5V: C1.1, C2.1, C3.1, J1.A2 (+5V), J1.B2 (+5V), U1.24 (VCC), U2.27 (~WE), U2.28 (VCC), U3.28 (VCC)
/ADDR0: J1.A22 (A0), U2.10 (A0), U3.10 (A0)
/ADDR1: J1.A19 (A1), U2.9 (A1), U3.9 (A1)
/ADDR2: J1.A17 (A2), U2.8 (A2), U3.8 (A2)
/ADDR3: J1.A15 (A3), U2.7 (A3), U3.7 (A3)
/ADDR4: J1.A14 (A4), U2.6 (A4), U3.6 (A4)
/ADDR5: J1.B9 (A5), U2.5 (A5), U3.5 (A5)
/ADDR6: J1.B7 (A6), U2.4 (A6), U3.4 (A6)
/ADDR7: J1.A4 (A7), U2.3 (A7), U3.3 (A7)
/ADDR8: J1.A8, U2.25 (A8), U3.25 (A8)
/ADDR9: J1.A9, U2.24 (A9), U3.24 (A9)
/ADDR10: J1.A18 (A10), U2.21 (A10), U3.21 (A10)
/ADDR11: J1.A13 (A11), U2.23 (A11), U3.23 (A11)
/ADDR12: J1.B3 (A12), U2.2 (A12), U3.2 (A12)
/ADDR13: J1.A6 (A13), U2.26 (A13), U3.26 (A13)
/ADDR14: J1.A3 (A14), U2.1 (A14), U3.1 (A14)
/DATABUS0: J1.A24 (D0), U2.11 (D0), U3.11 (DQ0)
/DATABUS1: J1.A27 (D1), U2.12 (D1), U3.12 (DQ1)
/DATABUS2: J1.A29 (D2), U2.13 (D2), U3.13 (DQ2)
/DATABUS3: J1.A32 (D3), U2.15 (D3), U3.15 (DQ3)
/DATABUS4: J1.A30 (D4), U2.16 (D4), U3.16 (DQ4)
/DATABUS5: J1.B27 (D5), U2.17 (D5), U3.17 (DQ5)
/DATABUS6: J1.A25 (D6), U2.18 (D6), U3.18 (DQ6)
/DATABUS7: J1.B22 (D7), U2.19 (D7), U3.19 (DQ7)
/~CE_LO: J1.A5 (/CE_LO), U1.2 (A15)
/~EE_OE: U1.20 (/EE_OE), U2.22 (~OE)
/~ROM_OE: J1.A16 (/ROM_OE), U3.22 (/OE)
/~SR_WE: U1.19 (/SR_WE), U3.27 (/WE)
GND: C1.2, C2.2, C3.2, J1.A1 (GND), J1.A11 (GND), J1.A21 (GND), J1.A31 (GND), J1.B1 (GND), J1.B10 (/CART), J1.B11 (GND), J1.B21 (GND), J1.B31 (GND), U1.12 (GND), U2.14 (GND), U2.20 (~CS), U3.14 (GND), U3.20 (/CE)
unnamed: J1.B4 (CLK), U1.1 (CLK)
unnamed: J1.B8 (PC_ENABLE), U1.4 (PC_ENABLE)
unnamed: J1.A7 (PIXEL_ENABLE), U1.3 (PIXEL_ENABLE)
unnamed: J1.B6 (RUN), U1.22 (RUN)
unnamed: J1.B12 (STALL_IN), U1.5 (STALL_IN)
unnamed: J1.B5 (STALL_OUT), U1.23 (STALL_OUT)

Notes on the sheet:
ROM cartridge, 32K
One EEPROM copied into one SRAM at power-up by the loader PLD (ROM.md, "Loading the cartridge")
U2 holds the 32K image, programmed off the board;
its /WE is tied high. U3 is the ROM the CPU
reads (15 ns). Both /CE are tied to GND: the
32K is seen in both halves (x0000 = x8000), and
the loader copies it twice. /CE_HI (B16) is
not used. The 64K cartridge is its own board
(kicad/cartridge_64k).
U1 stalls the CPU at each PC address
(STALL_OUT), pulses /SR_WE, lets the CPU
step, and raises RUN when the PC wraps.
/CART (B10) is tied to GND: cartridge present.
Spare contacts are unassigned (EXPANSION.md).

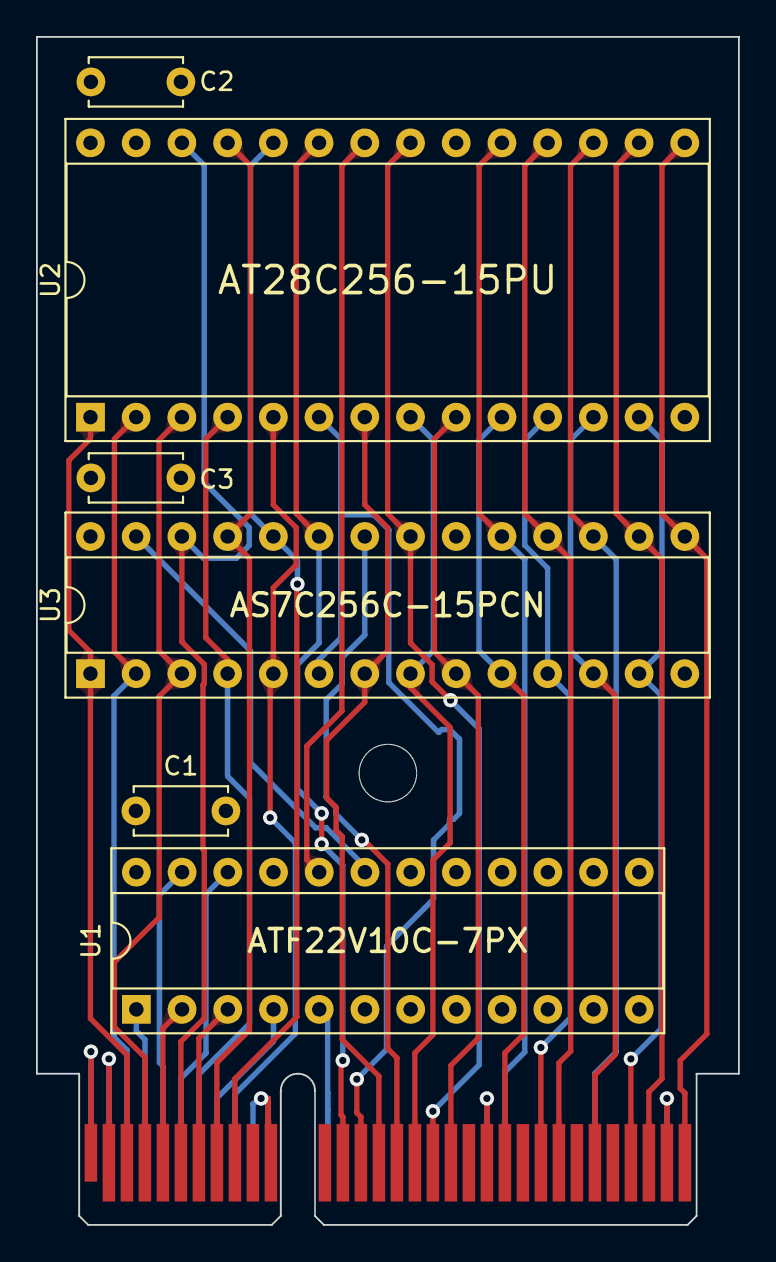
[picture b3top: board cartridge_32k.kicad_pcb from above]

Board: 4 copper layers, 39.0 x 66.0 mm, 8 parts (0 on the bottom side), 35 nets.

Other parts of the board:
H1: M3; MountingHole_3.2mm_M3

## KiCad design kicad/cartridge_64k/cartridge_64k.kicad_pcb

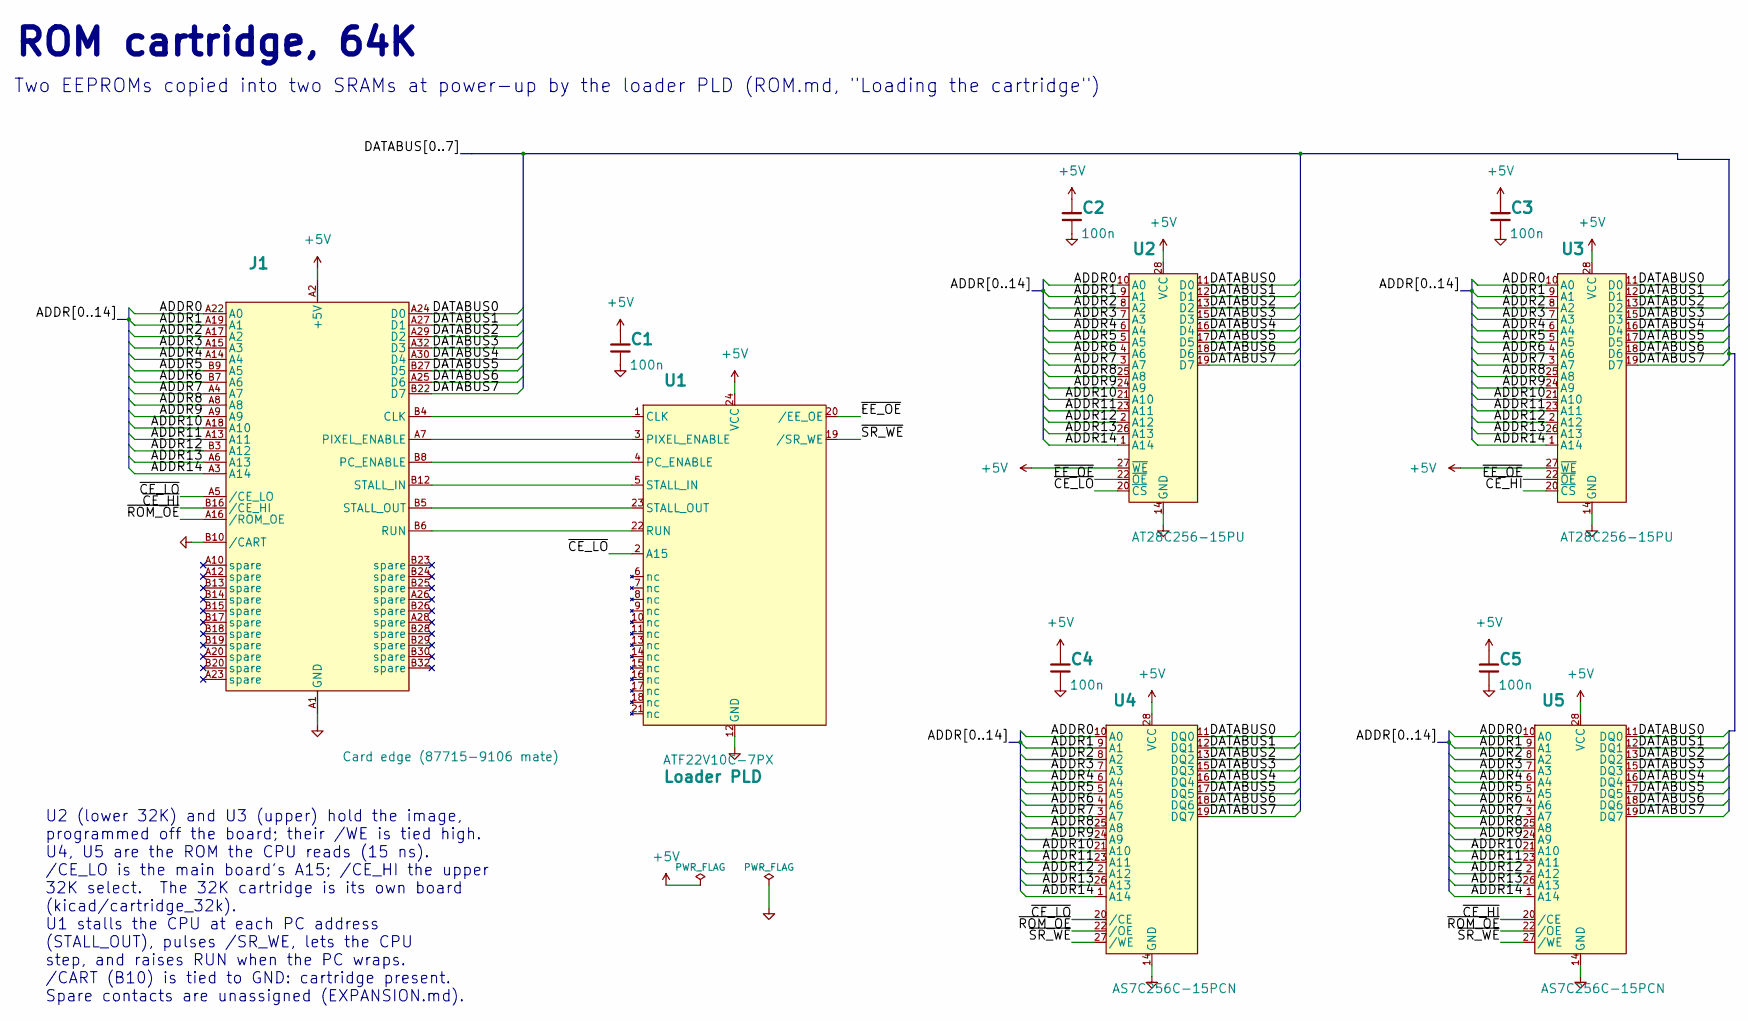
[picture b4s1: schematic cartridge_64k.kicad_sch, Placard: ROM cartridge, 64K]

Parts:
C1, C2, C3, C4, C5: 100n; C_Disc_D5.0mm_W2.5mm_P5.00mm; MPN FG28X7R1H104KNT00
J1: Card edge (87715-9106 mate); Card_Edge_87715-9106
U1: ATF22V10C-7PX; DIP-24_W7.62mm_Socket_Puller; MPN ATF22V10C-7PX
U2, U3: AT28C256-15PU; DIP-28_W15.24mm_Socket_Puller; MPN AT28C256-15PU
U4, U5: AS7C256C-15PCN; DIP-28_W7.62mm_Socket_Puller; MPN AS7C256C-15PCN

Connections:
+5V: C1.1, C2.1, C3.1, C4.1, C5.1, J1.A2 (+5V), J1.B2 (+5V), U1.24 (VCC), U2.27 (~WE), U2.28 (VCC), U3.27 (~WE), U3.28 (VCC), U4.28 (VCC), U5.28 (VCC)
/ADDR0: J1.A22 (A0), U2.10 (A0), U3.10 (A0), U4.10 (A0), U5.10 (A0)
/ADDR1: J1.A19 (A1), U2.9 (A1), U3.9 (A1), U4.9 (A1), U5.9 (A1)
/ADDR2: J1.A17 (A2), U2.8 (A2), U3.8 (A2), U4.8 (A2), U5.8 (A2)
/ADDR3: J1.A15 (A3), U2.7 (A3), U3.7 (A3), U4.7 (A3), U5.7 (A3)
/ADDR4: J1.A14 (A4), U2.6 (A4), U3.6 (A4), U4.6 (A4), U5.6 (A4)
/ADDR5: J1.B9 (A5), U2.5 (A5), U3.5 (A5), U4.5 (A5), U5.5 (A5)
/ADDR6: J1.B7 (A6), U2.4 (A6), U3.4 (A6), U4.4 (A6), U5.4 (A6)
/ADDR7: J1.A4 (A7), U2.3 (A7), U3.3 (A7), U4.3 (A7), U5.3 (A7)
/ADDR8: J1.A8, U2.25 (A8), U3.25 (A8), U4.25 (A8), U5.25 (A8)
/ADDR9: J1.A9, U2.24 (A9), U3.24 (A9), U4.24 (A9), U5.24 (A9)
/ADDR10: J1.A18 (A10), U2.21 (A10), U3.21 (A10), U4.21 (A10), U5.21 (A10)
/ADDR11: J1.A13 (A11), U2.23 (A11), U3.23 (A11), U4.23 (A11), U5.23 (A11)
/ADDR12: J1.B3 (A12), U2.2 (A12), U3.2 (A12), U4.2 (A12), U5.2 (A12)
/ADDR13: J1.A6 (A13), U2.26 (A13), U3.26 (A13), U4.26 (A13), U5.26 (A13)
/ADDR14: J1.A3 (A14), U2.1 (A14), U3.1 (A14), U4.1 (A14), U5.1 (A14)
/DATABUS0: J1.A24 (D0), U2.11 (D0), U3.11 (D0), U4.11 (DQ0), U5.11 (DQ0)
/DATABUS1: J1.A27 (D1), U2.12 (D1), U3.12 (D1), U4.12 (DQ1), U5.12 (DQ1)
/DATABUS2: J1.A29 (D2), U2.13 (D2), U3.13 (D2), U4.13 (DQ2), U5.13 (DQ2)
/DATABUS3: J1.A32 (D3), U2.15 (D3), U3.15 (D3), U4.15 (DQ3), U5.15 (DQ3)
/DATABUS4: J1.A30 (D4), U2.16 (D4), U3.16 (D4), U4.16 (DQ4), U5.16 (DQ4)
/DATABUS5: J1.B27 (D5), U2.17 (D5), U3.17 (D5), U4.17 (DQ5), U5.17 (DQ5)
/DATABUS6: J1.A25 (D6), U2.18 (D6), U3.18 (D6), U4.18 (DQ6), U5.18 (DQ6)
/DATABUS7: J1.B22 (D7), U2.19 (D7), U3.19 (D7), U4.19 (DQ7), U5.19 (DQ7)
/~CE_HI: J1.B16 (/CE_HI), U3.20 (~CS), U5.20 (/CE)
/~CE_LO: J1.A5 (/CE_LO), U1.2 (A15), U2.20 (~CS), U4.20 (/CE)
/~EE_OE: U1.20 (/EE_OE), U2.22 (~OE), U3.22 (~OE)
/~ROM_OE: J1.A16 (/ROM_OE), U4.22 (/OE), U5.22 (/OE)
/~SR_WE: U1.19 (/SR_WE), U4.27 (/WE), U5.27 (/WE)
GND: C1.2, C2.2, C3.2, C4.2, C5.2, J1.A1 (GND), J1.A11 (GND), J1.A21 (GND), J1.A31 (GND), J1.B1 (GND), J1.B10 (/CART), J1.B11 (GND), J1.B21 (GND), J1.B31 (GND), U1.12 (GND), U2.14 (GND), U3.14 (GND), U4.14 (GND), U5.14 (GND)
unnamed: J1.B4 (CLK), U1.1 (CLK)
unnamed: J1.B8 (PC_ENABLE), U1.4 (PC_ENABLE)
unnamed: J1.A7 (PIXEL_ENABLE), U1.3 (PIXEL_ENABLE)
unnamed: J1.B6 (RUN), U1.22 (RUN)
unnamed: J1.B12 (STALL_IN), U1.5 (STALL_IN)
unnamed: J1.B5 (STALL_OUT), U1.23 (STALL_OUT)

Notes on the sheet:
ROM cartridge, 64K
Two EEPROMs copied into two SRAMs at power-up by the loader PLD (ROM.md, "Loading the cartridge")
U2 (lower 32K) and U3 (upper) hold the image,
programmed off the board; their /WE is tied high.
U4, U5 are the ROM the CPU reads (15 ns).
/CE_LO is the main board's A15; /CE_HI the upper
32K select. The 32K cartridge is its own board
(kicad/cartridge_32k).
U1 stalls the CPU at each PC address
(STALL_OUT), pulses /SR_WE, lets the CPU
step, and raises RUN when the PC wraps.
/CART (B10) is tied to GND: cartridge present.
Spare contacts are unassigned (EXPANSION.md).

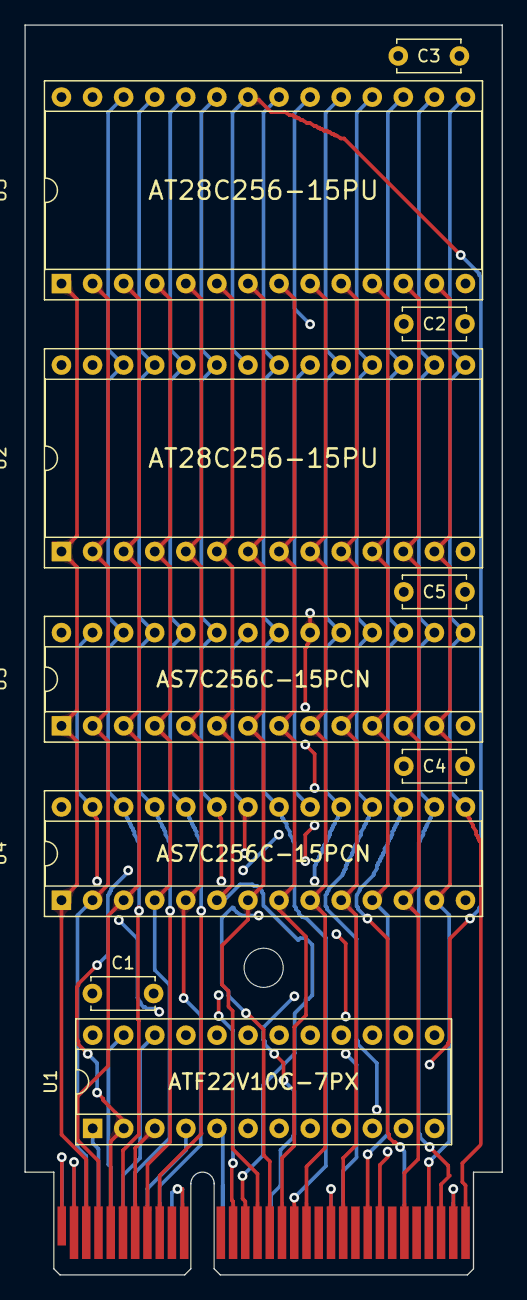
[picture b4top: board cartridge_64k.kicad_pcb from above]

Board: 4 copper layers, 39.0 x 102.2 mm, 12 parts (0 on the bottom side), 36 nets.

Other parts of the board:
H1: M3; MountingHole_3.2mm_M3

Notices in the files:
README.md:
License:
Placard is open hardware and open software.  Each kind of work has the license written for it:
Part | License
Hardware: the KiCad boards and schematics (`kicad/`, `schematics/`), the PLD equations and VHDL (`src/pld/`, `src/hdl/`, `src/sim/`) and the case (`case/`) | [CERN-OHL-S v2](LICENSES/CERN-OHL-S-2.0.txt)
Software: the ROM, BASIC, DOS, demos, games, tools and emulator (`src/scripts/`, `src/music/`, `sdcard/`, `web/`, `build/`) | [GPL v3 or later](LICENSES/GPL-3.0-or-later.txt)
Documentation and images (`README.md`, `docs/`, `reference/`) | [CC BY-SA 4.0
